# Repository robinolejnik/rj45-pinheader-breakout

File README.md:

# rj45-pinheader-breakout
2x RJ45 to pinheader breakout board

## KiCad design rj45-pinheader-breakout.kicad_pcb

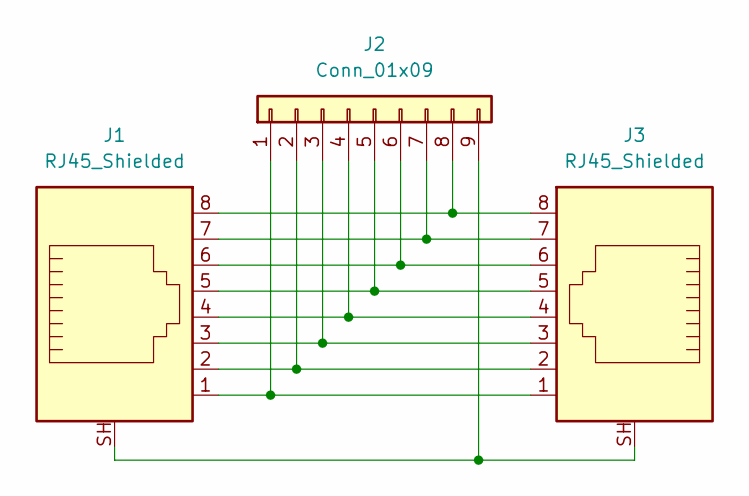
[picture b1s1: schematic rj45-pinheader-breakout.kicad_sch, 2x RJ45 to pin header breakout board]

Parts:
J1, J3: RJ45_Shielded; RJ45-multi
J2: Conn_01x09; PinHeader_1x09_P2.54mm_Vertical

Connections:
unnamed: J1.1, J2.1, J3.1
unnamed: J1.2, J2.2, J3.2
unnamed: J1.3, J2.3, J3.3
unnamed: J1.4, J2.4, J3.4
unnamed: J1.5, J2.5, J3.5
unnamed: J1.6, J2.6, J3.6
unnamed: J1.7, J2.7, J3.7
unnamed: J1.8, J2.8, J3.8
unnamed: J1.SH, J2.9, J3.SH

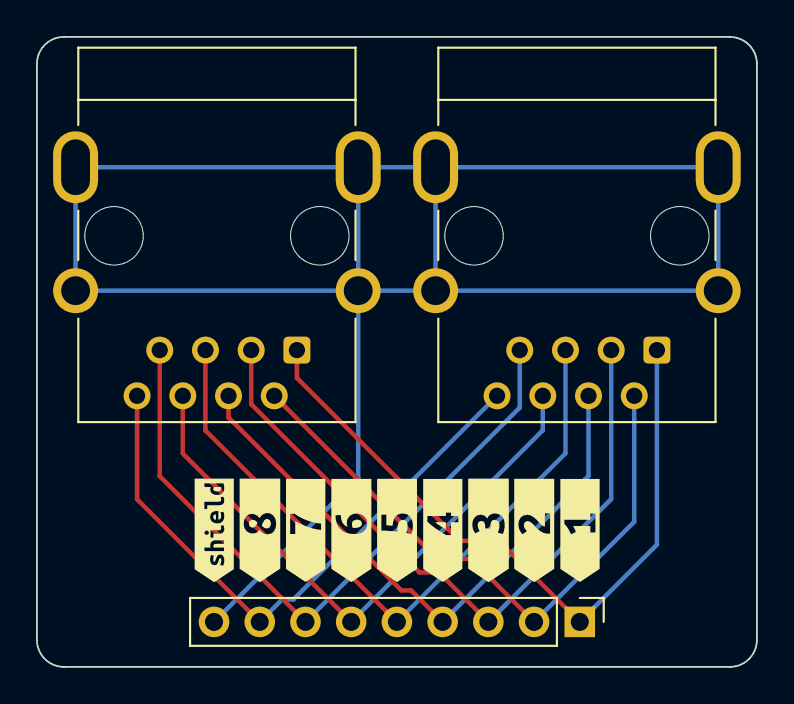
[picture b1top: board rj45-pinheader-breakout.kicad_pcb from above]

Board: 2 copper layers, 40.0 x 35.0 mm, 13 parts (1 on the bottom side), 9 nets.

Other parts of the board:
kibuzzard-62EAE7B5: G***; kibuzzard-62EAE7B5
kibuzzard-62EAE7BC: G***; kibuzzard-62EAE7BC
kibuzzard-62EAE7C3: G***; kibuzzard-62EAE7C3
kibuzzard-62EAE7C8: G***; kibuzzard-62EAE7C8
kibuzzard-62EAE7D9: G***; kibuzzard-62EAE7D9
kibuzzard-62EAE7E0: G***; kibuzzard-62EAE7E0
kibuzzard-62EAE7E7: G***; kibuzzard-62EAE7E7
kibuzzard-62EAE79F: G***; kibuzzard-62EAE79F
kibuzzard-62EAE686: G***; kibuzzard-62EAE686
kibuzzard-62EAE892: G***; kibuzzard-62EAE892

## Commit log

2022-08-03 Added KiCad files

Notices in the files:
rj45-pinheader-breakout.kicad_pcb:
License: CC0-1.0
